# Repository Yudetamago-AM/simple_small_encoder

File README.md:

# simple_small_encoder
A simple small encoder for CanSat.

This is not tested yet.

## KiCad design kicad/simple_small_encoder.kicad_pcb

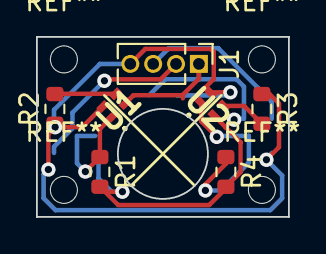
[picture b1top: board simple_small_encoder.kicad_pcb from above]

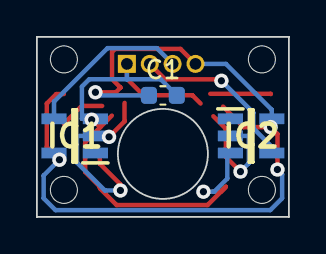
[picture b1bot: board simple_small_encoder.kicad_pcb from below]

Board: 2 copper layers, 14.0 x 10.0 mm, 10 parts (3 on the bottom side), 8 nets.

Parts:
C1: 0.1u; C_0603_1608Metric
IC1, IC2: TC7S14F_F_; SOT95P275X140-5N
J1: Conn_01x04_Male; PinHeader_1x04_P1.27mm_Vertical
R1, R4: 10k; R_0603_1608Metric
R2, R3: 220; R_0603_1608Metric
U1, U2: NJL5901AR; NJL5901AR1TE1

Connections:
+3V3: C1.1, IC1.5 (VCC), IC2.5 (VCC), J1.4, R2.1, R3.1, U1.4, U2.4
/OUT_A: IC1.4 (OUT_Y), J1.3
/OUT_A_raw: IC1.2 (IN_A), R4.1, U2.1
/OUT_B: IC2.4 (OUT_Y), J1.2
/OUT_B_raw: IC2.2 (IN_A), R1.1, U1.1
GND: C1.2, IC1.3 (GND), IC2.3 (GND), J1.1, R1.2, R4.2, U1.2, U2.2
unnamed: R2.2, U1.3
unnamed: R3.2, U2.3
